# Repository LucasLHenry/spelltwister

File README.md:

# spelltwister
Spelltwister is a dual function generator with a large palette of modulation algorithms. It has three modes: ENV (slow, single-cycle), LFO (slow, free-running), and VCO (fast, free-running). Each side of the module is a waveformer, which generates a signal controlled by three knobs. The basic structure of this signal is that of an AD envelope, so the signal first rises to it's maximum value (in a variable time and curvature), then falls back to it's minimum value (in a variable time and curvature). 

The three knobs are Time, Shape, and Ratio. Time controls the overall time for one cycle of the waveform, so also functions as pitch in VCO mode. Ratio controls the ratio between the time spent on the first stage versus the second stage (so ratio set fully CCW would mean that all time is spent falling, which would form a downwards saw wave). Lastly, Shape controls the curvature of the rising and falling, from exponential to logarithmic. With Shape in it's center position, the slope is linear, but turning it below 12 o'clock makes the rising and falling more exponential, while turning it the other way makes it more logarithmic.

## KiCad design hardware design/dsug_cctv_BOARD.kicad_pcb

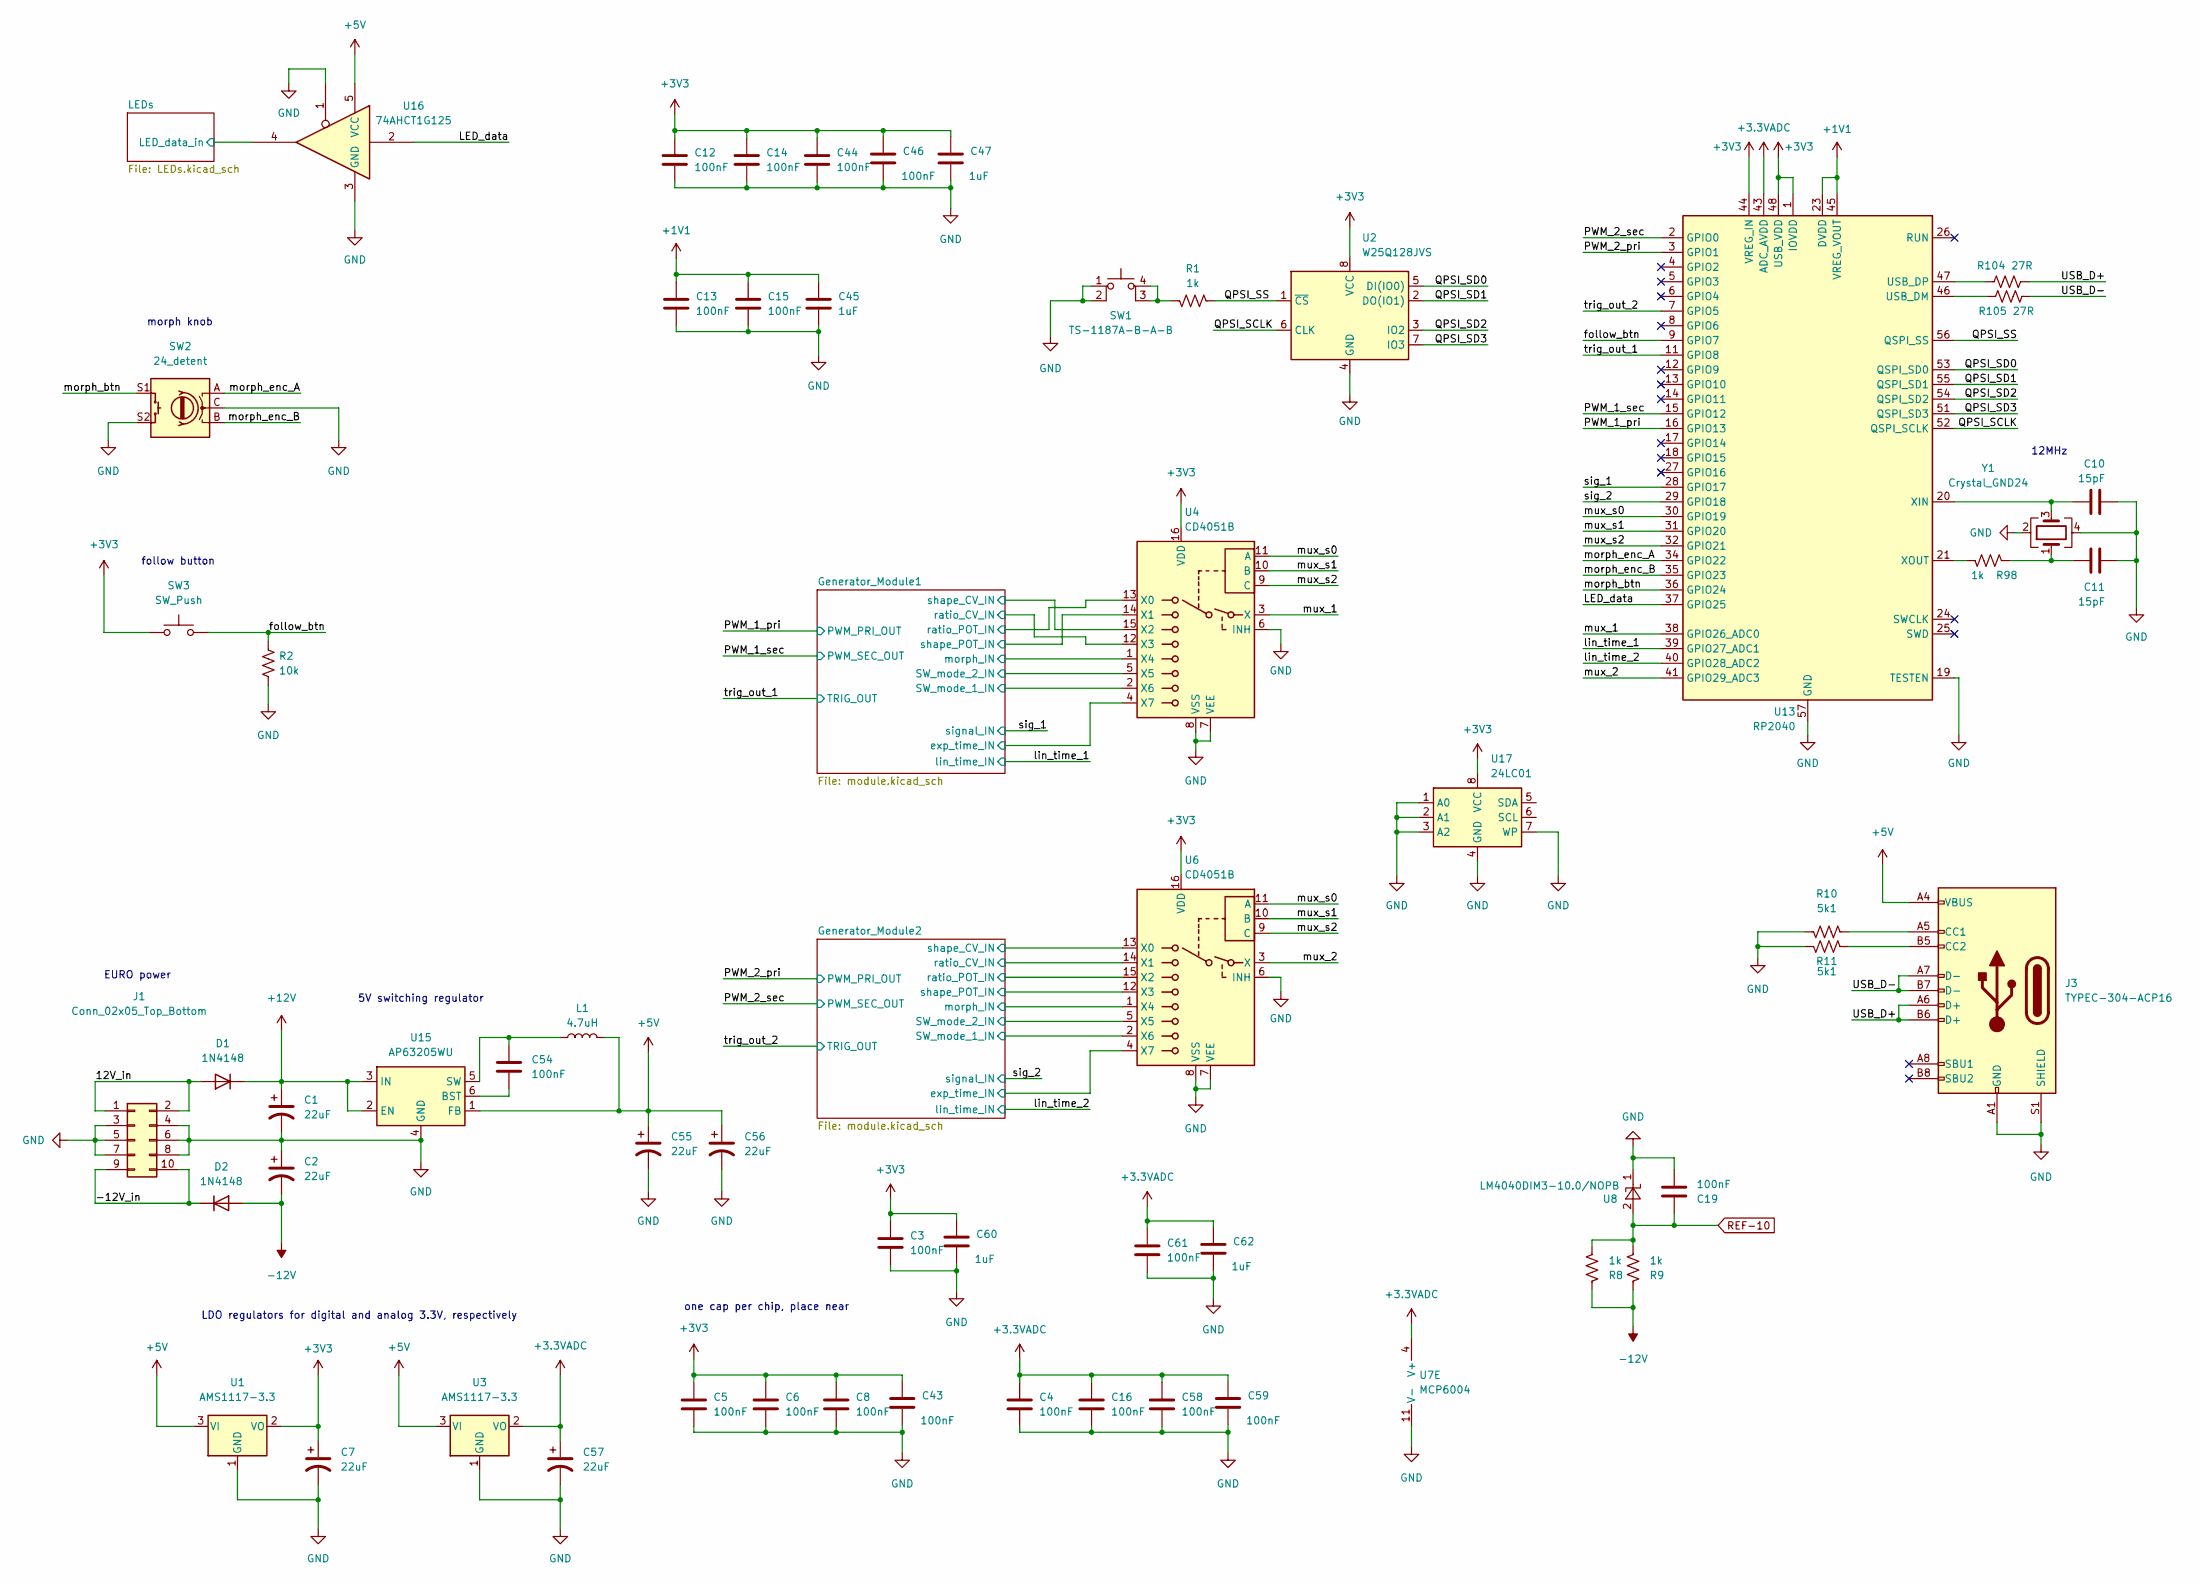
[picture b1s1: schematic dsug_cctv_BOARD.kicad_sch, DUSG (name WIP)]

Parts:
C1, C2, C7, C55, C56, C57: 22uF; CP_Radial_D5.0mm_P2.50mm
C3, C4, C5, C6, C8, C12, C13, C14, C15, C16, C19, C43, C44, C46, C54, C58, C59, C61: 100nF; C_0603_1608Metric
C10, C11: 15pF; C_0603_1608Metric
C45, C47, C60, C62: 1uF; C_0603_1608Metric
D1, D2: 1N4148; D_SOD-123
J1: Conn_02x05_Top_Bottom; PinHeader_2x05_P2.54mm_Vertical
J3: TYPEC-304-ACP16; USB_C_Receptacle_HRO_TYPE-C-31-M-12
L1: 4.7uH; L_TaiTech_HPC3010TF-4R7M
R1, R8, R9, R98: 1k; R_0603_1608Metric
R2: 10k; R_0603_1608Metric
R10, R11: 5k1; R_0603_1608Metric
R104, R105: 27R; R_0603_1608Metric
SW1: TS-1187A-B-A-B; push_switch_5.1x5.1
SW2: 24_detent; RotaryEncoder_Switch_Vertical_H20mm_20mm_knob
SW3: SW_Push; SW_PUSH_6mm
U1, U3: AMS1117-3.3; SOT-223-3_TabPin2
U2: W25Q128JVS; SOIC-8_5.23x5.23mm_P1.27mm
U4, U6: CD4051B; SOIC-16_3.9x9.9mm_P1.27mm
U7: MCP6004; SOIC-14_3.9x8.7mm_P1.27mm
U8: LM4040DIM3-10.0/NOPB; SOT-23
U13: RP2040; QFN-56-1EP_7x7mm_P0.4mm_EP3.2x3.2mm
U15: AP63205WU; TSOT-23-6
U16: 74AHCT1G125; SOT-353_SC-70-5
U17: 24LC01
Y1: Crystal_GND24; ABM8-272-T3_ABR

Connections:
+1V1: C13.1, C15.1, C45.1, U13.23 (DVDD), U13.45 (VREG_VOUT), U13.50 (DVDD)
+3.3VADC: C4.1, C16.1, C57.1, C58.1, C59.1, C61.1, C62.1, U3.2 (VO), U7.4 (V+), U13.43 (ADC_AVDD); also elsewhere on the board
+3V3: C3.1, C5.1, C6.1, C7.1, C8.1, C12.1, C14.1, C43.1, C44.1, C46.1, C47.1, C60.1, SW3.1, U1.2 (VO), U2.8 (VCC), U4.16 (VDD), U6.16 (VDD), U13.1 (IOVDD), U13.10 (IOVDD), U13.22 (IOVDD), U13.33 (IOVDD), U13.42 (IOVDD), U13.44 (VREG_IN), U13.48 (USB_VDD), U13.49 (IOVDD), U17.8 (VCC); also elsewhere on the board
+5V: C55.1, C56.1, J3.A4 (VBUS), J3.A9 (VBUS), J3.B4 (VBUS), J3.B9 (VBUS), L1.2, U1.3 (VI), U3.3 (VI), U15.1 (FB), U16.5 (VCC); also elsewhere on the board
+12V: C1.1, D1.1 (K), U15.2 (EN), U15.3 (IN); also elsewhere on the board
-12V: C2.2, D2.2 (A), R8.1, R9.1; also elsewhere on the board
/12V_in: D1.2 (A), J1.1, J1.2
/-12V_in: D2.1 (K), J1.9, J1.10
/Generator_Module1/SW_mode_1_IN: U4.2 (X6); also elsewhere on the board
/Generator_Module1/SW_mode_2_IN: U4.5 (X5); also elsewhere on the board
/Generator_Module1/exp_time_IN: U4.4 (X7); also elsewhere on the board
/Generator_Module1/morph_IN: U4.1 (X4); also elsewhere on the board
/Generator_Module1/ratio_CV_IN: U4.12 (X3); also elsewhere on the board
/Generator_Module1/ratio_pot: U4.13 (X0); also elsewhere on the board
/Generator_Module1/shape_CV_IN: U4.15 (X2); also elsewhere on the board
/Generator_Module1/shape_pot: U4.14 (X1); also elsewhere on the board
/Generator_Module2/SW_mode_1_IN: U6.2 (X6); also elsewhere on the board
/Generator_Module2/SW_mode_2_IN: U6.5 (X5); also elsewhere on the board
/Generator_Module2/exp_time_IN: U6.4 (X7); also elsewhere on the board
/Generator_Module2/morph_IN: U6.1 (X4), U7.14; also elsewhere on the board
/Generator_Module2/ratio_CV_IN: U6.14 (X1); also elsewhere on the board
/Generator_Module2/ratio_pot: U6.15 (X2); also elsewhere on the board
/Generator_Module2/shape_CV_IN: U6.13 (X0); also elsewhere on the board
/Generator_Module2/shape_pot: U6.12 (X3); also elsewhere on the board
/LED_data: U13.37 (GPIO25), U16.2
/LEDs/LED_data_in: U16.4; also elsewhere on the board
/PWM_1_pri: U13.16 (GPIO13); also elsewhere on the board
/PWM_1_sec: U13.15 (GPIO12); also elsewhere on the board
/PWM_2_pri: U13.3 (GPIO1); also elsewhere on the board
/PWM_2_sec: U13.2 (GPIO0); also elsewhere on the board
/QPSI_SCLK: U2.6 (CLK), U13.52 (QSPI_SCLK)
/QPSI_SD0: U2.5 (DI(IO0)), U13.53 (QSPI_SD0)
/QPSI_SD1: U2.2 (DO(IO1)), U13.55 (QSPI_SD1)
/QPSI_SD2: U2.3 (IO2), U13.54 (QSPI_SD2)
/QPSI_SD3: U2.7 (IO3), U13.51 (QSPI_SD3)
/QPSI_SS: R1.2, U2.1 (~CS), U13.56 (QSPI_SS)
/USB_D+: J3.A6 (D+), J3.B6 (D+), R104.2
/USB_D-: J3.A7 (D-), J3.B7 (D-), R105.2
/follow_btn: R2.1, SW3.2, U13.9 (GPIO7)
/lin_time_1: U13.39 (GPIO27_ADC1); also elsewhere on the board
/lin_time_2: U13.40 (GPIO28_ADC2); also elsewhere on the board
/morph_btn: SW2.S1, U13.36 (GPIO24)
/morph_enc_A: SW2.A, U13.34 (GPIO22)
/morph_enc_B: SW2.B, U13.35 (GPIO23)
/mux_1: U4.3 (X), U13.38 (GPIO26_ADC0)
/mux_2: U6.3 (X), U13.41 (GPIO29_ADC3)
/mux_s0: U4.11 (A), U6.11 (A), U13.30 (GPIO19)
/mux_s1: U4.10 (B), U6.10 (B), U13.31 (GPIO20)
/mux_s2: U4.9 (C), U6.9 (C), U13.32 (GPIO21)
/sig_1: U13.28 (GPIO17); also elsewhere on the board
/sig_2: U7.8, U13.29 (GPIO18); also elsewhere on the board
/trig_out_1: U13.11 (GPIO8); also elsewhere on the board
/trig_out_2: U13.7 (GPIO5); also elsewhere on the board
GND: C1.2, C2.1, C3.2, C4.2, C5.2, C6.2, C7.2, C8.2, C10.2, C11.2, C12.2, C13.2, C14.2, C15.2, C16.2, C19.2, C43.2, C44.2, C45.2, C46.2, C47.2, C55.2, C56.2, C57.2, C58.2, C59.2, C60.2, C61.2, C62.2, J1.3, J1.4, J1.5, J1.6, J1.7, J1.8, J3.A1 (GND), J3.A12 (GND), J3.B1 (GND), J3.B12 (GND), J3.S1 (SHIELD), R2.2, R10.2, R11.2, SW1.1, SW1.2, SW2.C, SW2.S2, U1.1 (GND), U2.4 (GND), U3.1 (GND), U4.6 (INH), U4.7 (VEE), U4.8 (VSS), U6.6 (INH), U6.7 (VEE), U6.8 (VSS), U7.10 (+), U7.11 (V-), U7.12 (+), U8.1 (K), U13.19 (TESTEN), U13.57 (GND), U15.4 (GND), U16.1, U16.3 (GND), U17.1 (A0), U17.2 (A1), U17.3 (A2), U17.4 (GND), U17.7 (WP), Y1.2, Y1.4; also elsewhere on the board
unnamed: C11.1, R98.1, Y1.1
unnamed: J3.A5 (CC1), R10.1
unnamed: J3.B5 (CC2), R11.1
unnamed: R1.1, SW1.3 (K), SW1.4 (A)
unnamed 140: U7.9 (-); also elsewhere on the board
unnamed 141: U7.13 (-); also elsewhere on the board
unnamed: R105.1, U13.46 (USB_DM)
unnamed: R104.1, U13.47 (USB_DP)
unnamed: C10.1, U13.20 (XIN), Y1.3
unnamed: R98.2, U13.21 (XOUT)
unnamed: C54.2, U15.6 (BST)
unnamed: C54.1, L1.1, U15.5 (SW)
REF-10: C19.1, R8.2, R9.2, U8.2 (A); also elsewhere on the board

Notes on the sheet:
one cap per chip, place near
5V switching regulator
LDO regulators for digital and analog 3.3V, respectively
EURO power
morph knob
12MHz
follow button

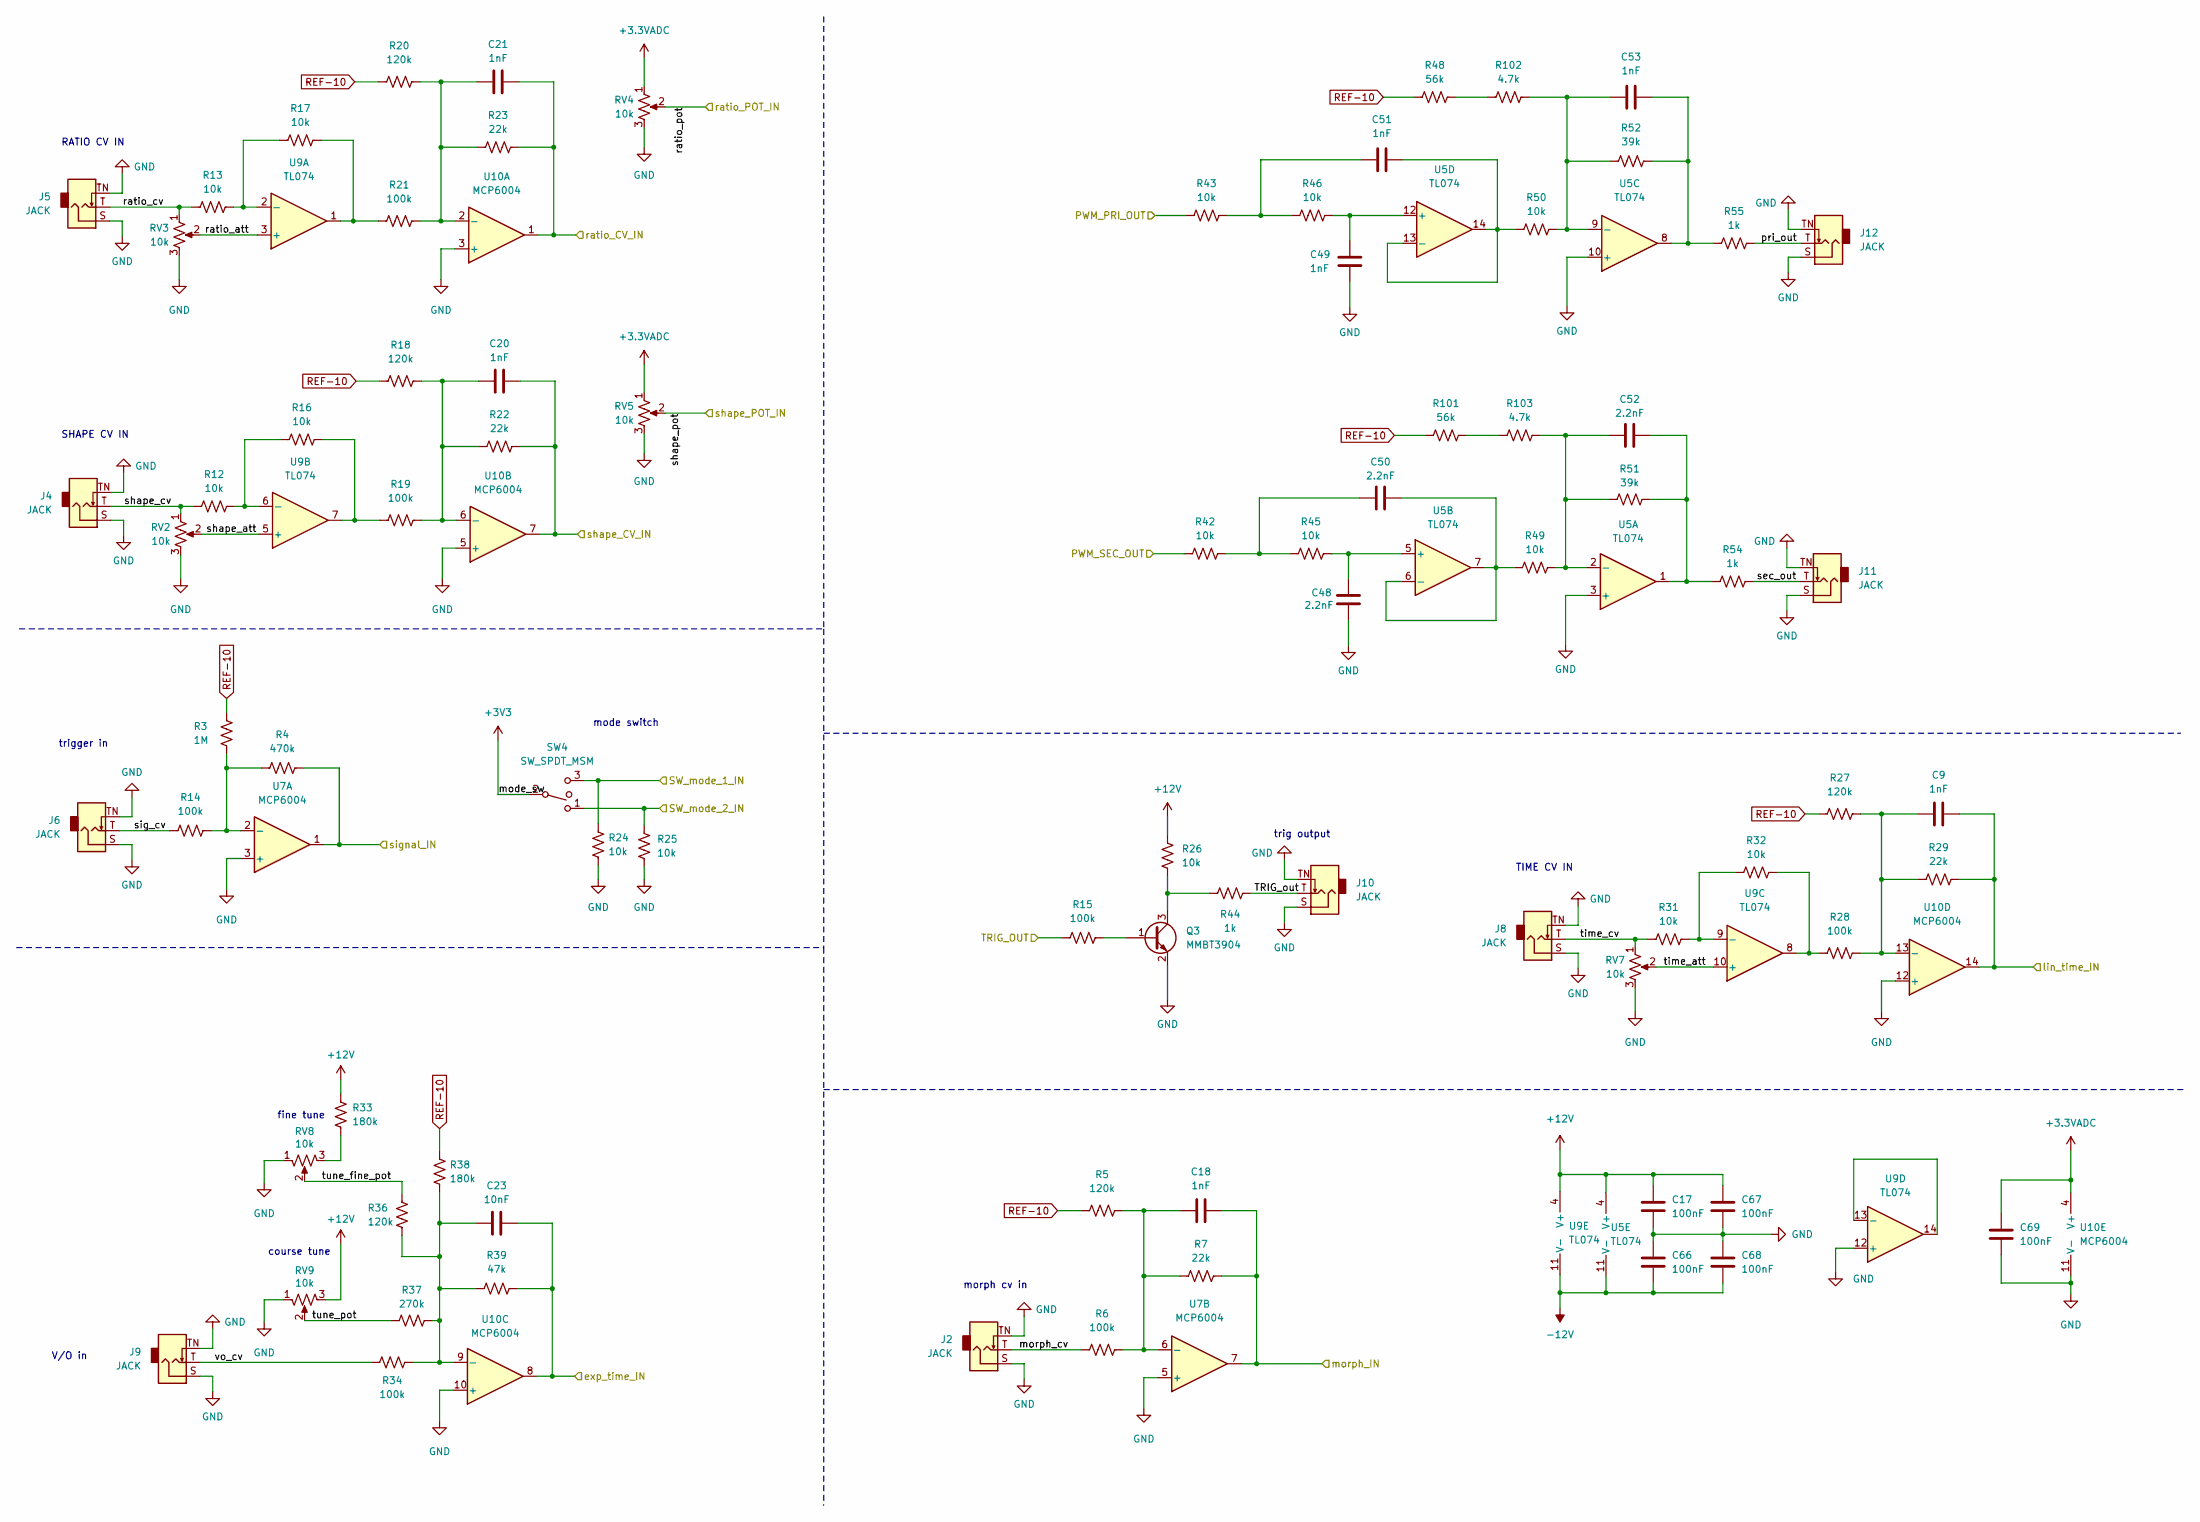
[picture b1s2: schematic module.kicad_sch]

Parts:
C9, C18, C20, C21, C49, C51, C53: 1nF; C_0603_1608Metric
C17, C66, C67, C68, C69: 100nF; C_0603_1608Metric
C23: 10nF; C_0603_1608Metric
C48, C50, C52: 2.2nF; C_0603_1608Metric
J2, J4, J5, J6, J8, J9, J10, J11, J12: JACK; AudioJack_3.5mm_with_drawing
Q3: MMBT3904; SOT-23
R3: 1M; R_0603_1608Metric
R4: 470k; R_0603_1608Metric
R5, R18, R20, R27, R36: 120k; R_0603_1608Metric
R6, R14, R15, R19, R21, R28, R34: 100k; R_0603_1608Metric
R7, R22, R23, R29: 22k; R_0603_1608Metric
R12, R13, R16, R17, R24, R25, R26, R31, R32, R42, R43, R45, R46, R49, R50: 10k; R_0603_1608Metric
R33, R38: 180k; R_0603_1608Metric
R37: 270k; R_0603_1608Metric
R39: 47k; R_0603_1608Metric
R44, R54, R55: 1k; R_0603_1608Metric
R48, R101: 56k; R_0603_1608Metric
R51, R52: 39k; R_0603_1608Metric
R102, R103: 4.7k; R_0603_1608Metric
RV2, RV3, RV7, RV8: 10k; Potentiometer_RV09_talltrimmer
RV4, RV5, RV9: 10k; Potentiometer_RV09_6mm_knob
SW4: SW_SPDT_MSM; SPDT_P2.54mm_Vertical
U5, U9: TL074; SOIC-14_3.9x8.7mm_P1.27mm
U7, U10: MCP6004; SOIC-14_3.9x8.7mm_P1.27mm

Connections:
+3.3VADC: C69.1, RV4.1, RV5.1, U10.4 (V+); also elsewhere on the board
+3V3: SW4.2; also elsewhere on the board
+12V: C17.1, C67.1, R26.1, R33.1, RV9.3, U5.4 (V+), U9.4 (V+); also elsewhere on the board
-12V: C66.2, C68.2, U5.11 (V-), U9.11 (V-); also elsewhere on the board
/Generator_Module1/SW_mode_1_IN: R24.1, SW4.3; also elsewhere on the board
/Generator_Module1/SW_mode_2_IN: R25.1, SW4.1; also elsewhere on the board
/Generator_Module1/TRIG_out: J10.T, R44.1
/Generator_Module1/exp_time_IN: C23.2, R39.2, U10.8; also elsewhere on the board
/Generator_Module1/morph_IN: C18.2, R7.2, U7.7; also elsewhere on the board
/Generator_Module1/morph_cv: J2.T, R6.1
/Generator_Module1/pri_out: J12.T, R55.2
/Generator_Module1/ratio_CV_IN: C21.2, R23.2, U10.1; also elsewhere on the board
/Generator_Module1/ratio_att: RV3.2, U9.3 (+)
/Generator_Module1/ratio_cv: J5.T, R13.1, RV3.1
/Generator_Module1/ratio_pot: RV4.2; also elsewhere on the board
/Generator_Module1/sec_out: J11.T, R54.2
/Generator_Module1/shape_CV_IN: C20.2, R22.2, U10.7; also elsewhere on the board
/Generator_Module1/shape_att: RV2.2, U9.5 (+)
/Generator_Module1/shape_cv: J4.T, R12.1, RV2.1
/Generator_Module1/shape_pot: RV5.2; also elsewhere on the board
/Generator_Module1/sig_cv: J6.T, R14.1
/Generator_Module1/time_att: RV7.2, U9.10 (+)
/Generator_Module1/time_cv: J8.T, R31.1, RV7.1
/Generator_Module1/tune_fine_pot: R36.1, RV8.2
/Generator_Module1/tune_pot: R37.1, RV9.2
/Generator_Module1/vo_cv: J9.T, R34.1
/Generator_Module2/morph_IN: U7.14; also elsewhere on the board
/PWM_1_pri: R43.1; also elsewhere on the board
/PWM_1_sec: R42.1; also elsewhere on the board
/lin_time_1: C9.2, R29.2, U10.14; also elsewhere on the board
/sig_1: R4.2, U7.1; also elsewhere on the board
/sig_2: U7.8; also elsewhere on the board
/trig_out_1: R15.1; also elsewhere on the board
GND: C17.2, C48.1, C49.2, C66.1, C67.2, C68.1, C69.2, J2.S, J2.TN, J4.S, J4.TN, J5.S, J5.TN, J6.S, J6.TN, J8.S, J8.TN, J9.S, J9.TN, J10.S, J10.TN, J11.S, J11.TN, J12.S, J12.TN, Q3.2 (E), R24.2, R25.2, RV2.3, RV3.3, RV4.3, RV5.3, RV7.3, RV8.1, RV9.1, U5.3 (+), U5.10 (+), U7.3 (+), U7.5 (+), U7.10 (+), U7.12 (+), U9.12 (+), U10.3 (+), U10.5 (+), U10.10 (+), U10.11 (V-), U10.12 (+); also elsewhere on the board
unnamed: C50.1, R42.2, R45.1
unnamed: C51.1, R43.2, R46.1
unnamed: C52.2, R51.2, R54.1, U5.1
unnamed: C53.2, R52.2, R55.1, U5.8
unnamed: Q3.1 (B), R15.2
unnamed: Q3.3 (C), R26.2, R44.2
unnamed: R16.2, R19.1, U9.7
unnamed: R17.2, R21.1, U9.1
unnamed: R28.1, R32.2, U9.8
unnamed: R33.2, RV8.3
unnamed: R101.2, R103.1
unnamed: R48.2, R102.1
unnamed: C52.1, R49.2, R51.1, R103.2, U5.2 (-)
unnamed: C48.2, R45.2, U5.5 (+)
unnamed: C50.2, R49.1, U5.6 (-), U5.7
unnamed: C53.1, R50.2, R52.1, R102.2, U5.9 (-)
unnamed: C49.1, R46.2, U5.12 (+)
unnamed: C51.2, R50.1, U5.13 (-), U5.14
unnamed: R3.1, R4.1, R14.2, U7.2 (-)
unnamed: C18.1, R5.2, R6.2, R7.1, U7.6 (-)
unnamed 140: U7.9 (-); also elsewhere on the board
unnamed 141: U7.13 (-); also elsewhere on the board
unnamed: R13.2, R17.1, U9.2 (-)
unnamed: R12.2, R16.1, U9.6 (-)
unnamed: R31.2, R32.1, U9.9 (-)
unnamed: U9.13 (-), U9.14
unnamed: C21.1, R20.2, R21.2, R23.1, U10.2 (-)
unnamed: C20.1, R18.2, R19.2, R22.1, U10.6 (-)
unnamed: C23.1, R34.2, R36.2, R37.2, R38.1, R39.1, U10.9 (-)
unnamed: C9.1, R27.2, R28.2, R29.1, U10.13 (-)
REF-10: R3.2, R5.1, R18.1, R20.1, R27.1, R38.2, R48.1, R101.1; also elsewhere on the board

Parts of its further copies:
C22: 10nF; C_0603_1608Metric
C28, C29, C30, C32, C34, C36, C41: 1nF; C_0603_1608Metric
C31, C33, C35: 2.2nF; C_0603_1608Metric
C37, C38, C39, C40, C42: 100nF; C_0603_1608Metric
J7, J13, J14, J15, J16, J17, J18, J19, J20: JACK; AudioJack_3.5mm_with_drawing
Q4: MMBT3904; SOT-23
R30: 1M; R_0603_1608Metric
R35, R59, R61, R63, R72, R74, R96: 100k; R_0603_1608Metric
R40, R41, R56, R57, R70, R71, R75, R77, R78, R80, R81, R86, R87, R91, R94: 10k; R_0603_1608Metric
R53: 470k; R_0603_1608Metric
R58, R66: 180k; R_0603_1608Metric
R60, R62, R64, R73, R95: 120k; R_0603_1608Metric
R65: 270k; R_0603_1608Metric
R67: 47k; R_0603_1608Metric
R68, R69, R76, R97: 22k; R_0603_1608Metric
R79, R92, R93: 1k; R_0603_1608Metric
R82, R83: 56k; R_0603_1608Metric
R84, R85: 4.7k; R_0603_1608Metric
R89, R90: 39k; R_0603_1608Metric
RV1, RV6, RV10, RV14: 10k; Potentiometer_RV09_talltrimmer
RV11, RV12, RV13: 10k; Potentiometer_RV09_6mm_knob
SW5: SW_SPDT_MSM; SPDT_P2.54mm_Vertical
U11: MCP6004; SOIC-14_3.9x8.7mm_P1.27mm
U12, U14: TL074; SOIC-14_3.9x8.7mm_P1.27mm

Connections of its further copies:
+3.3VADC: C42.1, RV12.1, RV13.1, U11.4 (V+); also elsewhere on the board
+3V3: SW5.2; also elsewhere on the board
+12V: C37.1, C39.1, R58.1, R75.1, RV11.3, U12.4 (V+), U14.4 (V+); also elsewhere on the board
-12V: C38.2, C40.2, U12.11 (V-), U14.11 (V-); also elsewhere on the board
/Generator_Module2/SW_mode_1_IN: R70.1, SW5.3; also elsewhere on the board
/Generator_Module2/SW_mode_2_IN: R71.1, SW5.1; also elsewhere on the board
/Generator_Module2/TRIG_out: J17.T, R79.1
/Generator_Module2/exp_time_IN: C22.2, R67.2, U11.8; also elsewhere on the board
/Generator_Module2/morph_IN: C30.2, R76.2; also elsewhere on the board
/Generator_Module2/morph_cv: J16.T, R74.1
/Generator_Module2/pri_out: J20.T, R93.2
/Generator_Module2/ratio_CV_IN: C28.2, R68.2, U11.1; also elsewhere on the board
/Generator_Module2/ratio_att: RV1.2, U12.3 (+)
/Generator_Module2/ratio_cv: J7.T, R40.1, RV1.1
/Generator_Module2/ratio_pot: RV13.2; also elsewhere on the board
/Generator_Module2/sec_out: J19.T, R92.2
/Generator_Module2/shape_CV_IN: C29.2, R69.2, U11.7; also elsewhere on the board
/Generator_Module2/shape_att: RV6.2, U12.5 (+)
/Generator_Module2/shape_cv: J13.T, R41.1, RV6.1
/Generator_Module2/shape_pot: RV12.2; also elsewhere on the board
/Generator_Module2/sig_cv: J14.T, R35.1
/Generator_Module2/time_att: RV14.2, U12.10 (+)
/Generator_Module2/time_cv: J18.T, R91.1, RV14.1
/Generator_Module2/tune_fine_pot: R64.1, RV10.2
/Generator_Module2/tune_pot: R65.1, RV11.2
/Generator_Module2/vo_cv: J15.T, R59.1
/PWM_2_pri: R78.1; also elsewhere on the board
/PWM_2_sec: R77.1; also elsewhere on the board
/lin_time_2: C41.2, R97.2, U11.14; also elsewhere on the board
/sig_2: R53.2; also elsewhere on the board
/trig_out_2: R72.1; also elsewhere on the board
GND: C31.1, C32.2, C37.2, C38.1, C39.2, C40.1, C42.2, J7.S, J7.TN, J13.S, J13.TN, J14.S, J14.TN, J15.S, J15.TN, J16.S, J16.TN, J17.S, J17.TN, J18.S, J18.TN, J19.S, J19.TN, J20.S, J20.TN, Q4.2 (E), R70.2, R71.2, RV1.3, RV6.3, RV10.1, RV11.1, RV12.3, RV13.3, RV14.3, U11.3 (+), U11.5 (+), U11.10 (+), U11.11 (V-), U11.12 (+), U12.12 (+), U14.5 (+), U14.12 (+); also elsewhere on the board
unnamed: C33.1, R77.2, R80.1
unnamed: C34.1, R78.2, R81.1
unnamed: C35.2, R89.2, R92.1, U14.14
unnamed: C36.2, R90.2, R93.1, U14.7
unnamed: Q4.1 (B), R72.2
unnamed: Q4.3 (C), R75.2, R79.2
unnamed: R56.2, R61.1, U12.1
unnamed: R57.2, R63.1, U12.7
unnamed: R58.2, RV10.3
unnamed: R82.2, R84.1
unnamed: R83.2, R85.1
unnamed: R94.2, R96.1, U12.8
unnamed 140: R30.1, R35.2, R53.1; also elsewhere on the board
unnamed 141: C30.1, R73.2, R74.2, R76.1; also elsewhere on the board
unnamed: C28.1, R60.2, R61.2, R68.1, U11.2 (-)
unnamed: C29.1, R62.2, R63.2, R69.1, U11.6 (-)
unnamed: C22.1, R59.2, R64.2, R65.2, R66.1, R67.1, U11.9 (-)
unnamed: C41.1, R95.2, R96.2, R97.1, U11.13 (-)
unnamed: R40.2, R56.1, U12.2 (-)
unnamed: R41.2, R57.1, U12.6 (-)
unnamed: R91.2, R94.1, U12.9 (-)
unnamed: U12.13 (-), U12.14
unnamed: C32.1, R81.2, U14.3 (+)
unnamed: C34.2, R87.1, U14.1, U14.2 (-)
unnamed: C36.1, R84.2, R87.2, R90.1, U14.6 (-)
unnamed: C31.2, R80.2, U14.10 (+)
unnamed: C33.2, R86.1, U14.8, U14.9 (-)
unnamed: C35.1, R85.2, R86.2, R89.1, U14.13 (-)
REF-10: R30.2, R60.1, R62.1, R66.2, R73.1, R82.1, R83.1, R95.1; also elsewhere on the board

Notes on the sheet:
course tune
morph cv in
trig output
SHAPE CV IN
V/O in
fine tune
RATIO CV IN
mode switch
TIME CV IN
trigger in

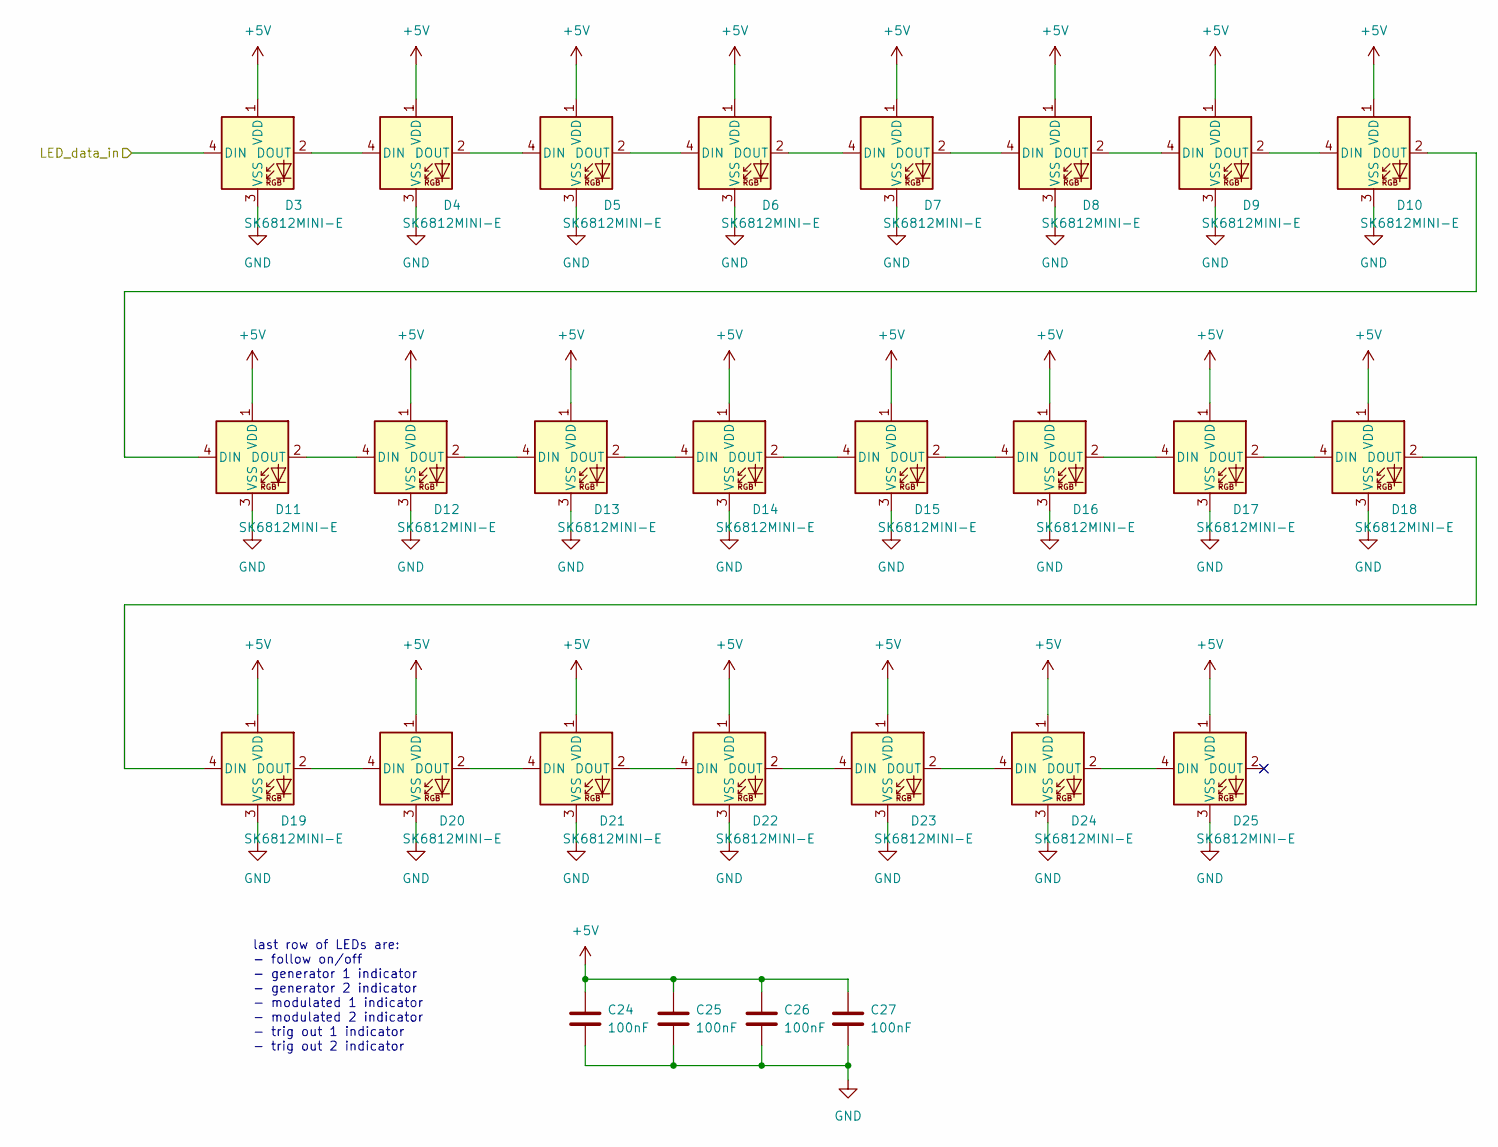
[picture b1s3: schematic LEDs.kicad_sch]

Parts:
C24, C25, C26, C27: 100nF; C_0603_1608Metric
D3, D4, D5, D6, D7, D8, D9, D10, D11, D12, D13, D14, D15, D16, D17, D18, D19, D20, D21, D22, D23, D24, D25: SK6812MINI-E; SK6812MINIE

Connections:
+5V: C24.1, C25.1, C26.1, C27.1, D3.1 (VDD), D4.1 (VDD), D5.1 (VDD), D6.1 (VDD), D7.1 (VDD), D8.1 (VDD), D9.1 (VDD), D10.1 (VDD), D11.1 (VDD), D12.1 (VDD), D13.1 (VDD), D14.1 (VDD), D15.1 (VDD), D16.1 (VDD), D17.1 (VDD), D18.1 (VDD), D19.1 (VDD), D20.1 (VDD), D21.1 (VDD), D22.1 (VDD), D23.1 (VDD), D24.1 (VDD), D25.1 (VDD); also elsewhere on the board
/LEDs/LED_data_in: D3.4 (DIN); also elsewhere on the board
GND: C24.2, C25.2, C26.2, C27.2, D3.3 (VSS), D4.3 (VSS), D5.3 (VSS), D6.3 (VSS), D7.3 (VSS), D8.3 (VSS), D9.3 (VSS), D10.3 (VSS), D11.3 (VSS), D12.3 (VSS), D13.3 (VSS), D14.3 (VSS), D15.3 (VSS), D16.3 (VSS), D17.3 (VSS), D18.3 (VSS), D19.3 (VSS), D20.3 (VSS), D21.3 (VSS), D22.3 (VSS), D23.3 (VSS), D24.3 (VSS), D25.3 (VSS); also elsewhere on the board
unnamed: D3.2 (DOUT), D4.4 (DIN)
unnamed: D4.2 (DOUT), D5.4 (DIN)
unnamed: D5.2 (DOUT), D6.4 (DIN)
unnamed: D6.2 (DOUT), D7.4 (DIN)
unnamed: D7.2 (DOUT), D8.4 (DIN)
unnamed: D8.2 (DOUT), D9.4 (DIN)
unnamed: D9.2 (DOUT), D10.4 (DIN)
unnamed: D10.2 (DOUT), D11.4 (DIN)
unnamed: D11.2 (DOUT), D12.4 (DIN)
unnamed: D12.2 (DOUT), D13.4 (DIN)
unnamed: D13.2 (DOUT), D14.4 (DIN)
unnamed: D14.2 (DOUT), D15.4 (DIN)
unnamed: D15.2 (DOUT), D16.4 (DIN)
unnamed: D16.2 (DOUT), D17.4 (DIN)
unnamed: D17.2 (DOUT), D18.4 (DIN)
unnamed: D18.2 (DOUT), D19.4 (DIN)
unnamed: D19.2 (DOUT), D20.4 (DIN)
unnamed: D20.2 (DOUT), D21.4 (DIN)
unnamed: D21.2 (DOUT), D22.4 (DIN)
unnamed: D22.2 (DOUT), D23.4 (DIN)
unnamed: D23.2 (DOUT), D24.4 (DIN)
unnamed: D24.2 (DOUT), D25.4 (DIN)

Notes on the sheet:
last row of LEDs are: - follow on/off - generator 1 indicator - generator 2 indicator - modulated 1 indicator - modulated 2 indicator - trig out 1 indicator - trig out 2 indicator

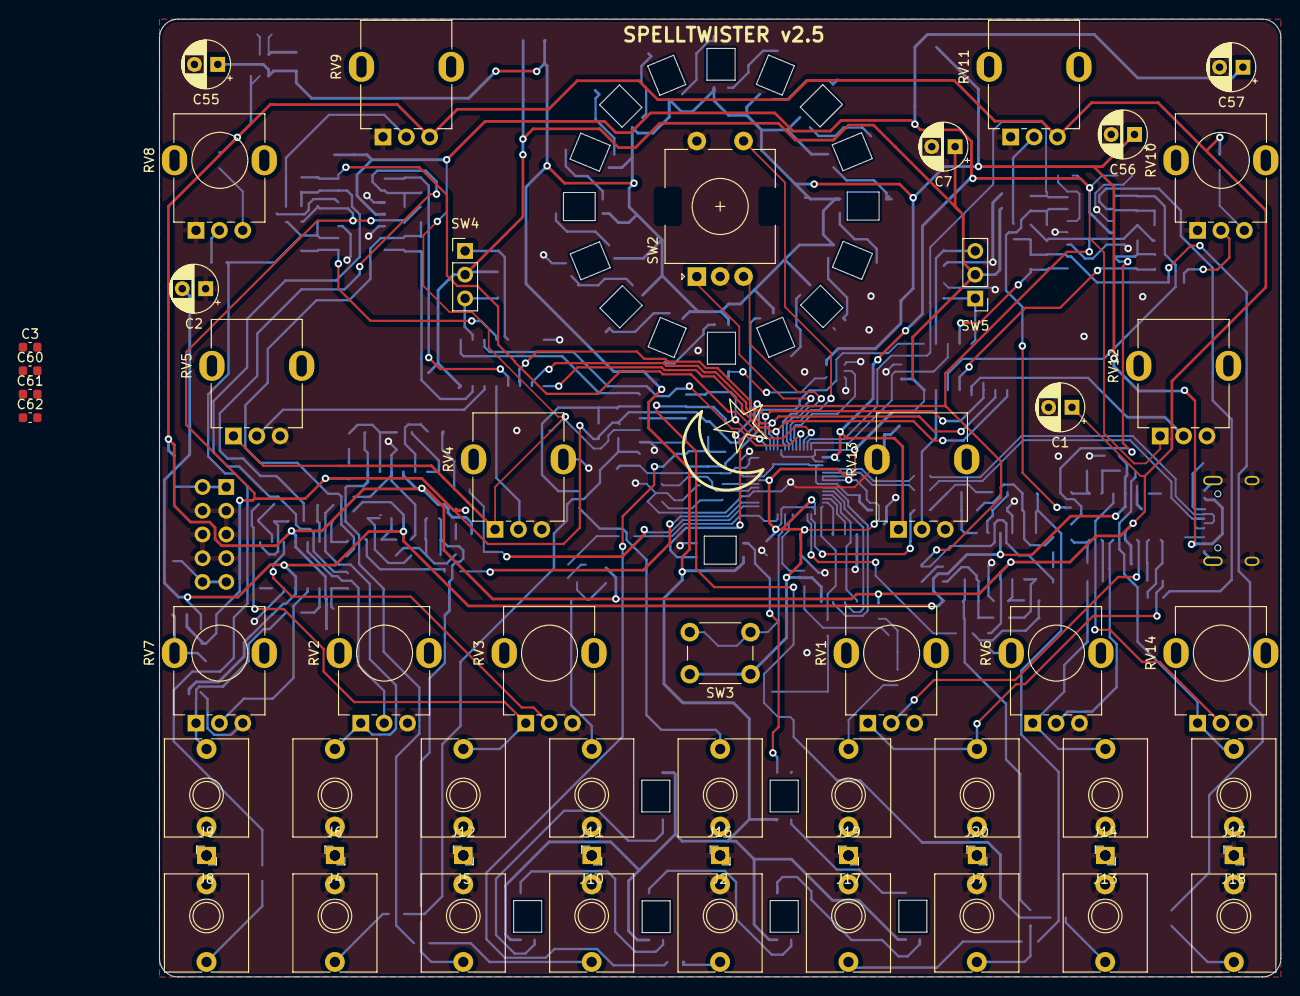
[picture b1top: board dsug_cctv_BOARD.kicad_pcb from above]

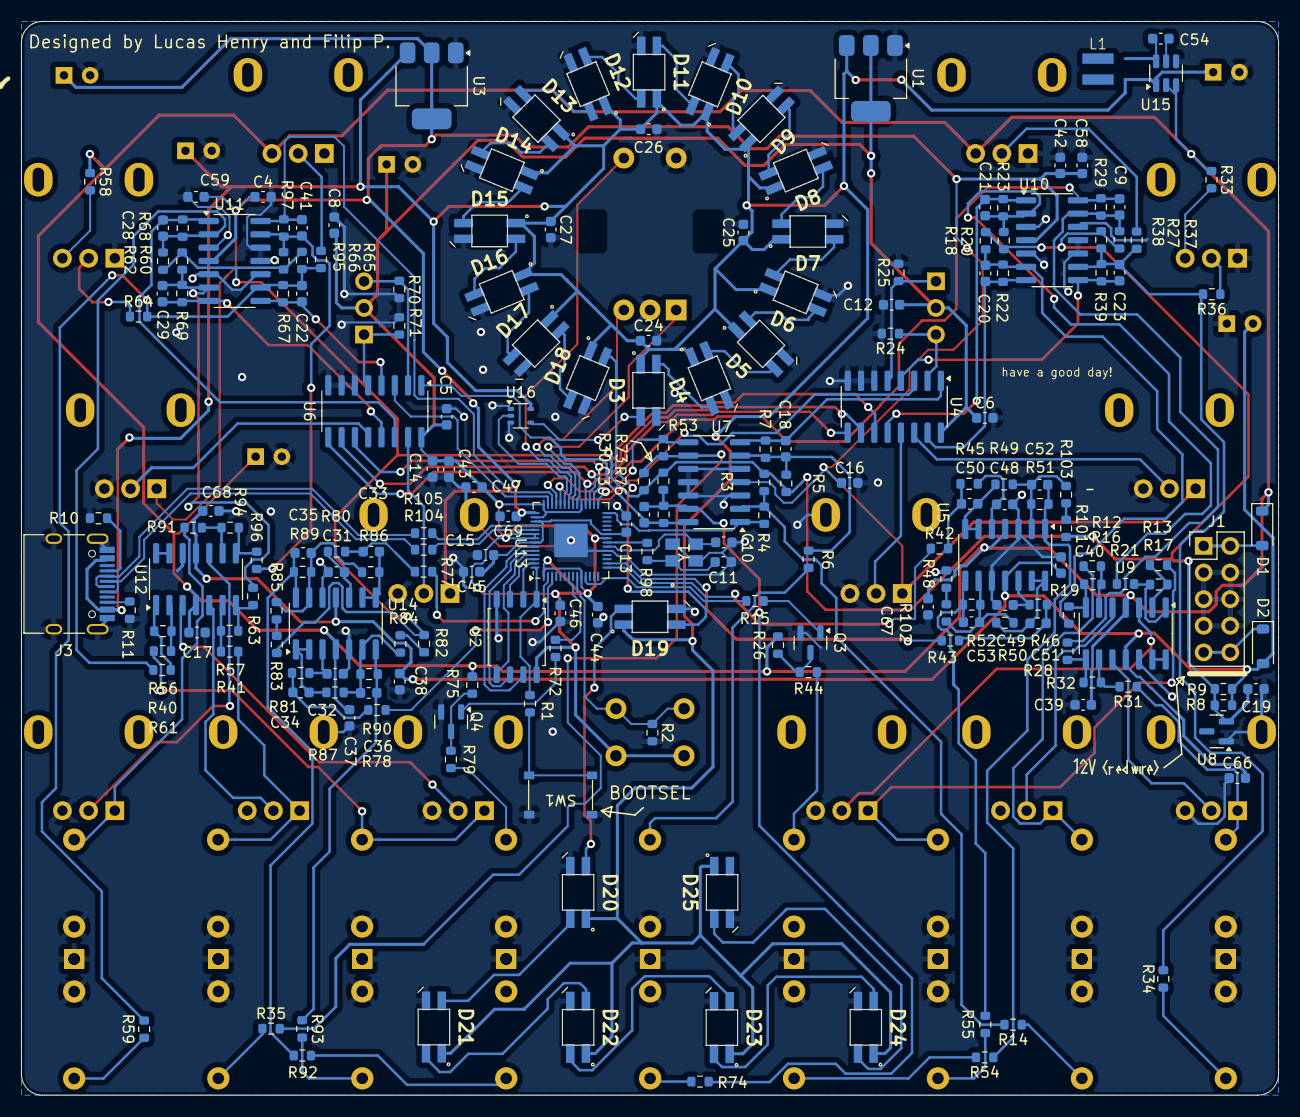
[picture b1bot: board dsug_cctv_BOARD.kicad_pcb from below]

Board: 2 copper layers, 120.0 x 102.5 mm, 251 parts (205 on the bottom side), 171 nets.

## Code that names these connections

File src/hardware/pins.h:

// pin assignments for the SAM D21
// use these names to refer to them
#ifndef PINS_H
#define PINS_H


#define LIN_TIME_A 27
#define SIG_IN_A 17
#define MUX_A 26
#define PRI_OUT_A 13  // don't know what PWM reg this corresponds to
#define SEC_OUT_A 12  // same as above
#define TRIG_OUT_A 8

#define LIN_TIME_B 28
#define SIG_IN_B 18
#define MUX_B 29
#define PRI_OUT_B 1  // don't know what PWM reg this corresponds to
#define SEC_OUT_B 0  // same as above
#define TRIG_OUT_B 5

#define LED_PIN 25
#define LED_DATA {LED_PIN, -1, -1, -1, -1, -1, -1, -1}

#define ALGO_ENC_1 23
#define ALGO_ENC_2 22
#define ALGO_BTN 24
#define FLW_BTN 7

#define MUX_S0 19
#define MUX_S1 20
#define MUX_S2 21

// led assignments
#define NUM_LEDS 23
#define NUM_RING_LEDS 16
#define FLW_LED 16
#define TRIG_B_LED 17
#define PRI_B_LED 18
#define SEC_B_LED 19
#define SEC_A_LED 20
#define PRI_A_LED 21
#define TRIG_A_LED 22

// mux A assignments
#define R_CV_A   3
#define R_POT_A  0
#define S_CV_A   2
#define S_POT_A  1
#define M_CV_A   4
#define SW_1_A   5
#define SW_2_A   6
#define EXP_CV_A 7

// mux B assignments
#define R_CV_B   1
#define R_POT_B  2
#define S_CV_B   0
#define S_POT_B  3
#define M_CV_B   4
#define SW_1_B   5
#define SW_2_B   6
#define EXP_CV_B 7

#endif
